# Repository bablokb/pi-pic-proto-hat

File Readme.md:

The Pi-PIC-Proto-Hat (Version 2)
================================

Overview
--------

One of the shortcomings of the Pi is it's inability to turn off power after
shutdown. While the Pi itself only drains a small amount of power, attached
peripherals might draw a lot more. At irregular intervals, the Pi also
fails to shutdown the USB-connector, so USB-devices can really use large
amounts of power even when the Pi has shutdown.

One solution is to pull the plug, another one uses a mosfet controlled by
a microcontroller to turn power on and off. The MCU typically uses its
GPIOs to receive external signals for power on and off. In its simplest
form such a signal is just a button pulling the GPIO to ground.

The pi-pic-proto-hat provides the wiring for a PIC12F675 (MCU) and the
IRF4905 (mosfet). In addition, there is a small prototyping area for
buttons, sensors and alike.

If you are more familiar with a different family of MCUs (e.g. Atmega), you
should modify the design of the pcb. The Kicad-sources are in the
directory `pi-pic-proto-hat.kicad`.

Design
------

The design consists mainly of the two parts "power supply" and "PIC".
The PIC part

is a fairly standard implementation for the PIC featuring an
ICSP (in-circuit-programming) connector J8. GP2 and GP4 are connected to
connector, GP4 in addition to a switch and the interupt-pin of the RTC.
GP3 is only connected to the ICSP connector and unused otherwise.

If you are not using a MCU of the PIC-family, this is the part you must
modify to fit your preferred MCU.

The power-supply part

connects a barrel-jack J6 (5mm/2.1mm-type) to the mosfet, which controls
the 5V and 3.3V connectors of the Pi. J6 is also connected to J3/J11, which
give you 5V independent of the state of the Pi. In addition, if you
populate the 1117-regulator (U2), you also have permanent 3.3V on
connectors J4/J5.

The IRF4905 mosfet will switch power efficiently as long as the voltage
of the gate is high enough. The 5V of the MCU is sufficient and the
mosfet will not get too warm with the typical currents needed by a Pi.

The pcb also provides access to most of the GPIOs of the Pi. In addition,
there is a prototyping area and a number of GND-pins and power pins
(5V and 3,3V).

Note that the project-directory contains a Fritzing-template
(prototype-template.fzz) which is useful for prototyping:

Manufacturing
-------------

If your pcb-manufacturer supports Kicad directly, you can just upload the
project-file. Otherwise you have to start Kicad and export ("plot") the
gerber-files for the pcb (gerber is a universal format understood by all
manufacturers).

When you use the existing pcb-layout without any modifications, you should
make sure that you have the correct parts available. Most critical is the
barrel-jack footprint. The pcb is designed for the CUI_PJ_102AH. This part
is available e.g. from Adafruit. It looks like a normal barrel-jack adapter
but has smaller pins so you can use it directly on a breadboard.

Part-List
---------

|Part                | Value           | Number | Remark               |
|--------------------|-----------------|--------|----------------------|
|C1,C4               | 100nF/50V       | 2      | SMD 1206             |
|C2,C3               | 10µF            | 2      | SMD 1206 Tantal      |
|D1,D2               | LED             | 2      | SMD 1206             |
|J1-J5,J7-13         | SL 1x40G 2,54mm | 2      | vertical             |
|J6 (barral jack)    | CUI_PJ_102AH    | 1      | Adafruit             |
|P1 (Pi-socket)      | BL 2x20G 2,54mm | 1      | vertical             |
|Q1                  | IRF4905         | 1      | TO-220AB             |
|R1,R6               | 10k             | 2      | SMD 1206             |
|R2,R3,R4,R5         | 1k              | 4      | SMD 1206             |
|R7                  | 6.2k            | 1      | SMD 1206             |
|R8                  | 12k             | 1      | SMD 1206             |
|SW1                 |                 | 1      | slim switch          |
|U1                  | PIC12F675-IP    | 1      | SO-8                 |
|U2                  | TLV1117-33      | 1      | SOT-223 (or AMS1117) |
|U3                  | DS3231M         | 1      | SOIC-16W             |

Wiring
------

Not all parts are necessary, e.g. you don't need to populate the RTC
or the regulator. The two LEDs D2 (active power-supply) and D1 (power
is provided to the Pi) are also optional (together with their resistors).

You need to close jumper J1 (Run/~PGM) during normal operation. If you
flash the firmware, this jumper should be open.

Please be careful not to power the hat and the Pi at the same time.

Flashing a Firmware
-------------------

The required firmware for the PIC depends on the specific setup you choose.
In the directory [pic-firmware](./pic-firmware/Readme.md)
you will find a ready to flash hex-file for the PIC.

For flashing, you need a PICkit2-programmer, available for a few bucks from
ebay. You can flash from Linux/Raspbian with the program `pk2cmd`. The hat
has a connector for the ICSP-programmer. You should remove the jumper-shim
on J1 (connection to Pi) during programming.

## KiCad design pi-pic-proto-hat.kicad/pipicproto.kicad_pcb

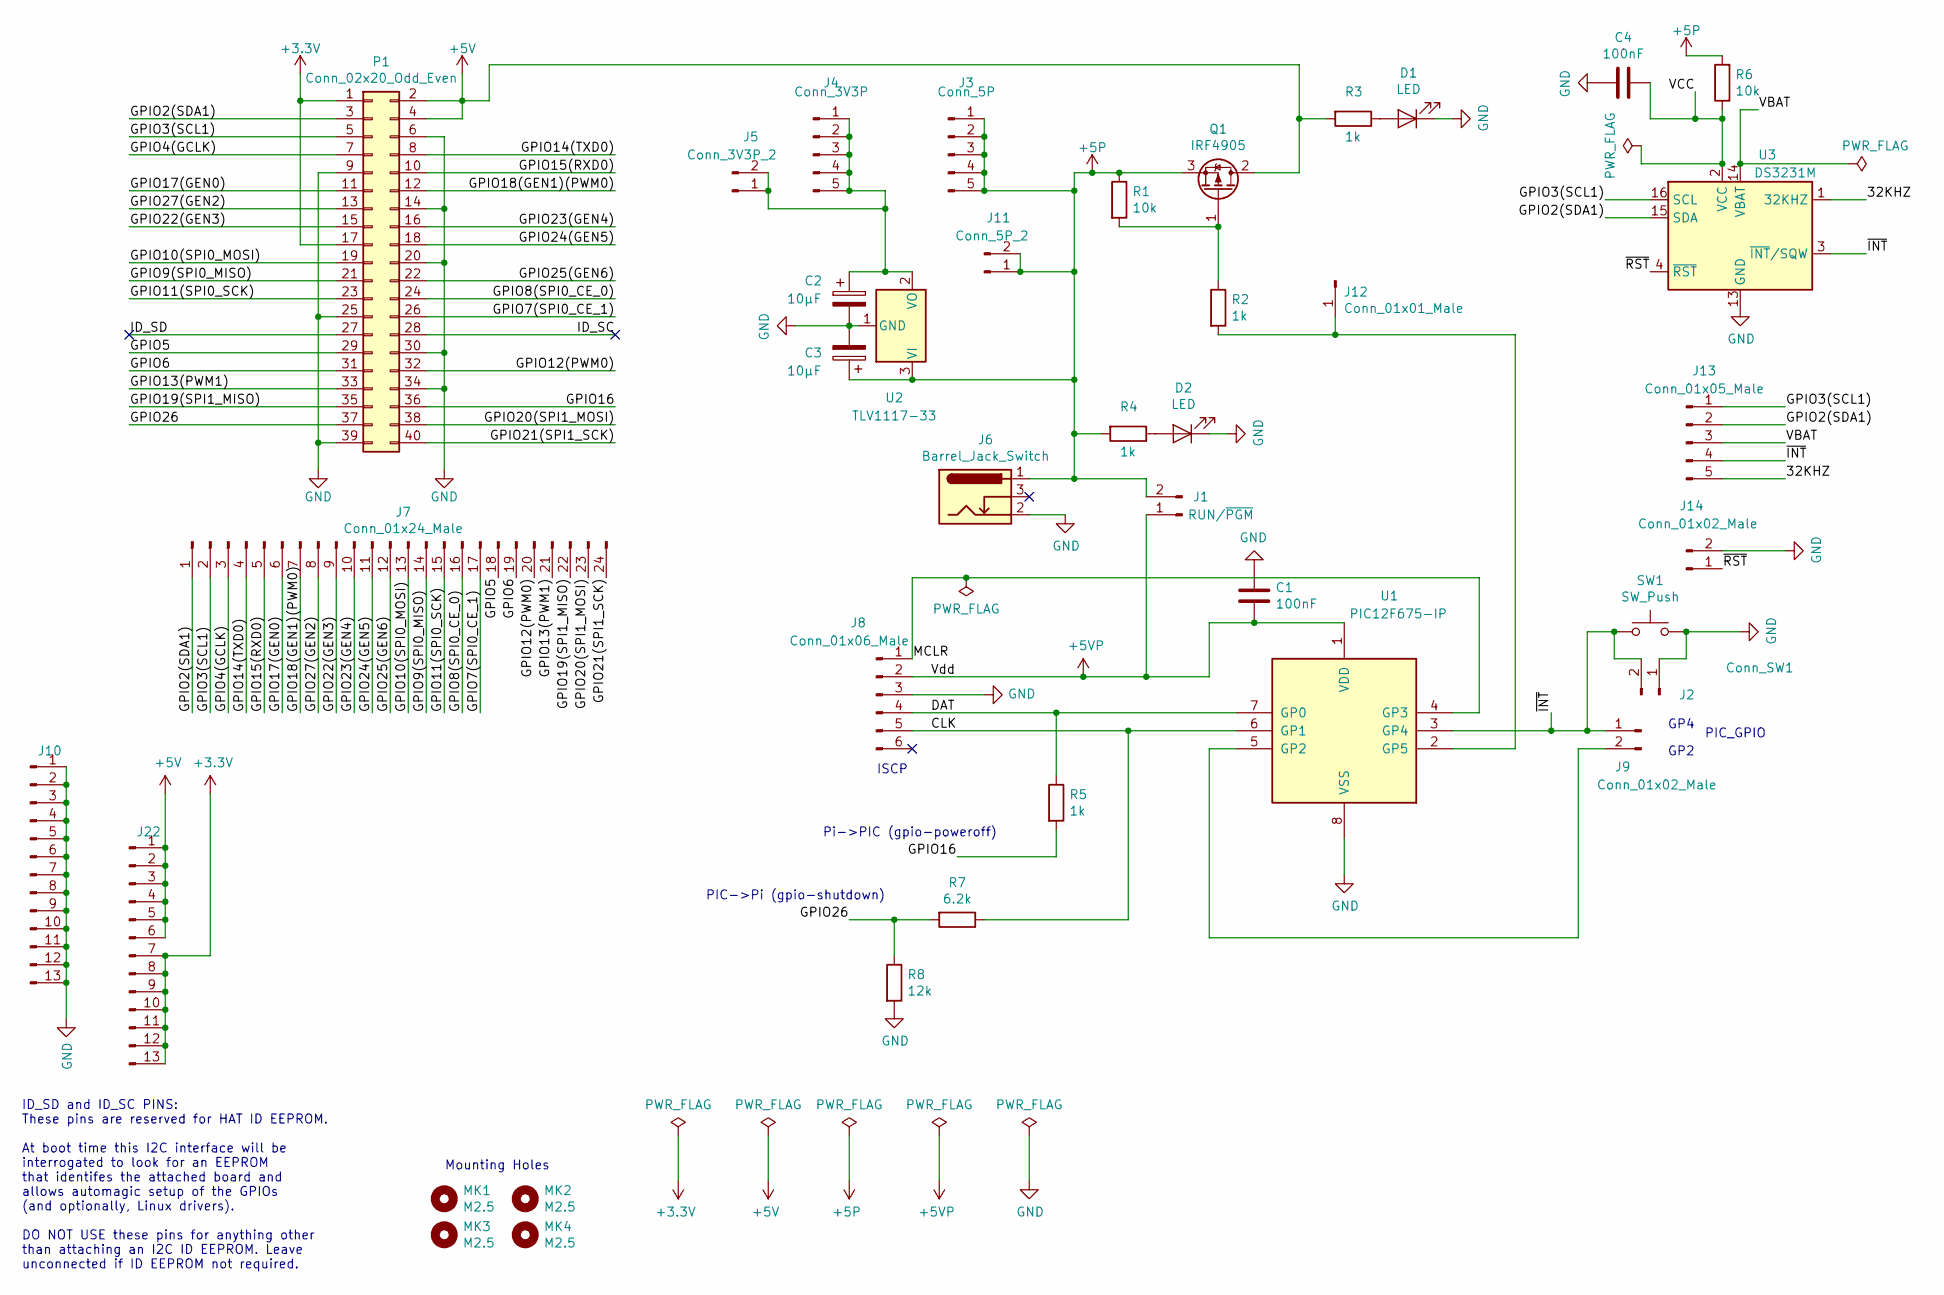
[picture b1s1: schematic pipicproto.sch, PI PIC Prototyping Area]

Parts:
C1, C4: 100nF; C_1206_3216Metric_Pad1.42x1.75mm_HandSolder
C2, C3: 10µF; CP_EIA-3216-18_Kemet-A
D1, D2: LED; LED_1206_3216Metric_Pad1.42x1.75mm_HandSolder
J1: RUN/~PGM~; PinHeader_1x02_P2.54mm_Vertical
J2: Conn_SW1; PinHeader_1x02_P2.54mm_Vertical
J3: Conn_5P; PinHeader_1x05_P2.54mm_Vertical
J4: Conn_3V3P; PinHeader_1x05_P2.54mm_Vertical
J5: Conn_3V3P_2; PinHeader_1x02_P2.54mm_Vertical
J6: Barrel_Jack_Switch; BarrelJack_CUI_PJ-102AH_Horizontal
J7: Conn_01x24_Male; PinHeader_1x24_P2.54mm_Vertical
J8: Conn_01x06_Male; PinHeader_1x06_P2.54mm_Vertical
J9, J14: Conn_01x02_Male; PinHeader_1x02_P2.54mm_Vertical
J10, J22: Conn_01x13_Male; PinHeader_1x13_P2.54mm_Vertical
J11: Conn_5P_2; PinHeader_1x02_P2.54mm_Vertical
J12: Conn_01x01_Male; PinHeader_1x01_P2.54mm_Vertical
J13: Conn_01x05_Male; PinHeader_1x05_P2.54mm_Vertical
MK1, MK2, MK3, MK4: M2.5; MountingHole_2.7mm_M2.5
P1: Conn_02x20_Odd_Even; PinSocket_2x20_P2.54mm_Vertical
Q1: IRF4905; TO-220-3_Vertical
R1, R6: 10k; R_1206_3216Metric_Pad1.42x1.75mm_HandSolder
R2, R3, R4, R5: 1k; R_1206_3216Metric_Pad1.42x1.75mm_HandSolder
R7: 6.2k; R_1206_3216Metric_Pad1.42x1.75mm_HandSolder
R8: 12k; R_1206_3216Metric_Pad1.42x1.75mm_HandSolder
SW1: SW_Push; SW_PUSH_SLIM_1x4
U1: PIC12F675-IP; SO-8_3.9x4.9mm_P1.27mm
U2: TLV1117-33; SOT-223
U3: DS3231M; SOIC-16W_7.5x10.3mm_P1.27mm

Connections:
+3V3: J22.7, J22.8, J22.9, J22.10, J22.11, J22.12, J22.13, P1.1, P1.17
+5P: C3.1, J1.2, J3.1, J3.2, J3.3, J3.4, J3.5, J6.1, J11.1, J11.2, Q1.3 (S), R1.1, R4.2, R6.2, U2.3 (VI)
+5V: J22.1, J22.2, J22.3, J22.4, J22.5, J22.6, P1.2, P1.4, Q1.2 (D), R3.2
+5VP: C1.2, J1.1, J8.2, U1.1 (VDD)
/32KHZ: J13.5, U3.1 (32KHZ)
/CLK: J8.5, R7.1, U1.6 (GP1)
/DAT: J8.4, R5.1, U1.7 (GP0)
/GPIO2(SDA1): J7.1, J13.2, P1.3, U3.15 (SDA)
/GPIO3(SCL1): J7.2, J13.1, P1.5, U3.16 (SCL)
/GPIO4(GCLK): J7.3, P1.7
/GPIO5: J7.18, P1.29
/GPIO6: J7.19, P1.31
/GPIO7(SPI0_CE_1): J7.17, P1.26
/GPIO8(SPI0_CE_0): J7.16, P1.24
/GPIO9(SPI0_MISO): J7.14, P1.21
/GPIO10(SPI0_MOSI): J7.13, P1.19
/GPIO11(SPI0_SCK): J7.15, P1.23
/GPIO12(PWM0): J7.20, P1.32
/GPIO13(PWM1): J7.21, P1.33
/GPIO14(TXD0): J7.4, P1.8
/GPIO15(RXD0): J7.5, P1.10
/GPIO16: P1.36, R5.2
/GPIO17(GEN0): J7.6, P1.11
/GPIO18(GEN1)(PWM0): J7.7, P1.12
/GPIO19(SPI1_MISO): J7.22, P1.35
/GPIO20(SPI1_MOSI): J7.23, P1.38
/GPIO21(SPI1_SCK): J7.24, P1.40
/GPIO22(GEN3): J7.9, P1.15
/GPIO23(GEN4): J7.10, P1.16
/GPIO24(GEN5): J7.11, P1.18
/GPIO25(GEN6): J7.12, P1.22
/GPIO26: P1.37, R7.2, R8.1
/GPIO27(GEN2): J7.8, P1.13
/ID_SC: P1.28
/ID_SD: P1.27
/MCLR: J8.1, U1.4 (GP3)
/VBAT: J13.3, U3.14 (VBAT)
/VCC: C4.1, R6.1, U3.2 (VCC)
/~INT: J2.2, J9.1, J13.4, SW1.1, U1.3 (GP4), U3.3 (~INT~/SQW)
/~RST: J14.1, U3.4 (~RST)
GND: C1.1, C2.2, C3.2, C4.2, D1.1 (K), D2.1 (K), J2.1, J6.2, J8.3, J10.1, J10.2, J10.3, J10.4, J10.5, J10.6, J10.7, J10.8, J10.9, J10.10, J10.11, J10.12, J10.13, J14.2, P1.6, P1.9, P1.14, P1.20, P1.25, P1.30, P1.34, P1.39, R8.2, SW1.2, U1.8 (VSS), U2.1 (GND), U3.5 (GND), U3.6 (GND), U3.7 (GND), U3.8 (GND), U3.9 (GND), U3.10 (GND), U3.11 (GND), U3.12 (GND), U3.13 (GND)
unnamed: C2.1, J4.1, J4.2, J4.3, J4.4, J4.5, J5.1, J5.2, U2.2 (VO)
unnamed: D1.2 (A), R3.1
unnamed: D2.2 (A), R4.1
unnamed: J9.2, U1.5 (GP2)
unnamed: J12.1, R2.2, U1.2 (GP5)
unnamed: Q1.1 (G), R1.2, R2.1

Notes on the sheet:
ID_SD and ID_SC PINS: These pins are reserved for HAT ID EEPROM. At boot time this I2C interface will be interrogated to look for an EEPROM that identifes the attached board and allows automagic setup of the GPIOs (and optionally, Linux drivers). DO NOT USE these pins for anything other than attach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
Mounting Holes
PIC_GPIO
ISCP
Pi->PIC (gpio-poweroff)
PIC->Pi (gpio-shutdown)
GP4
GP2

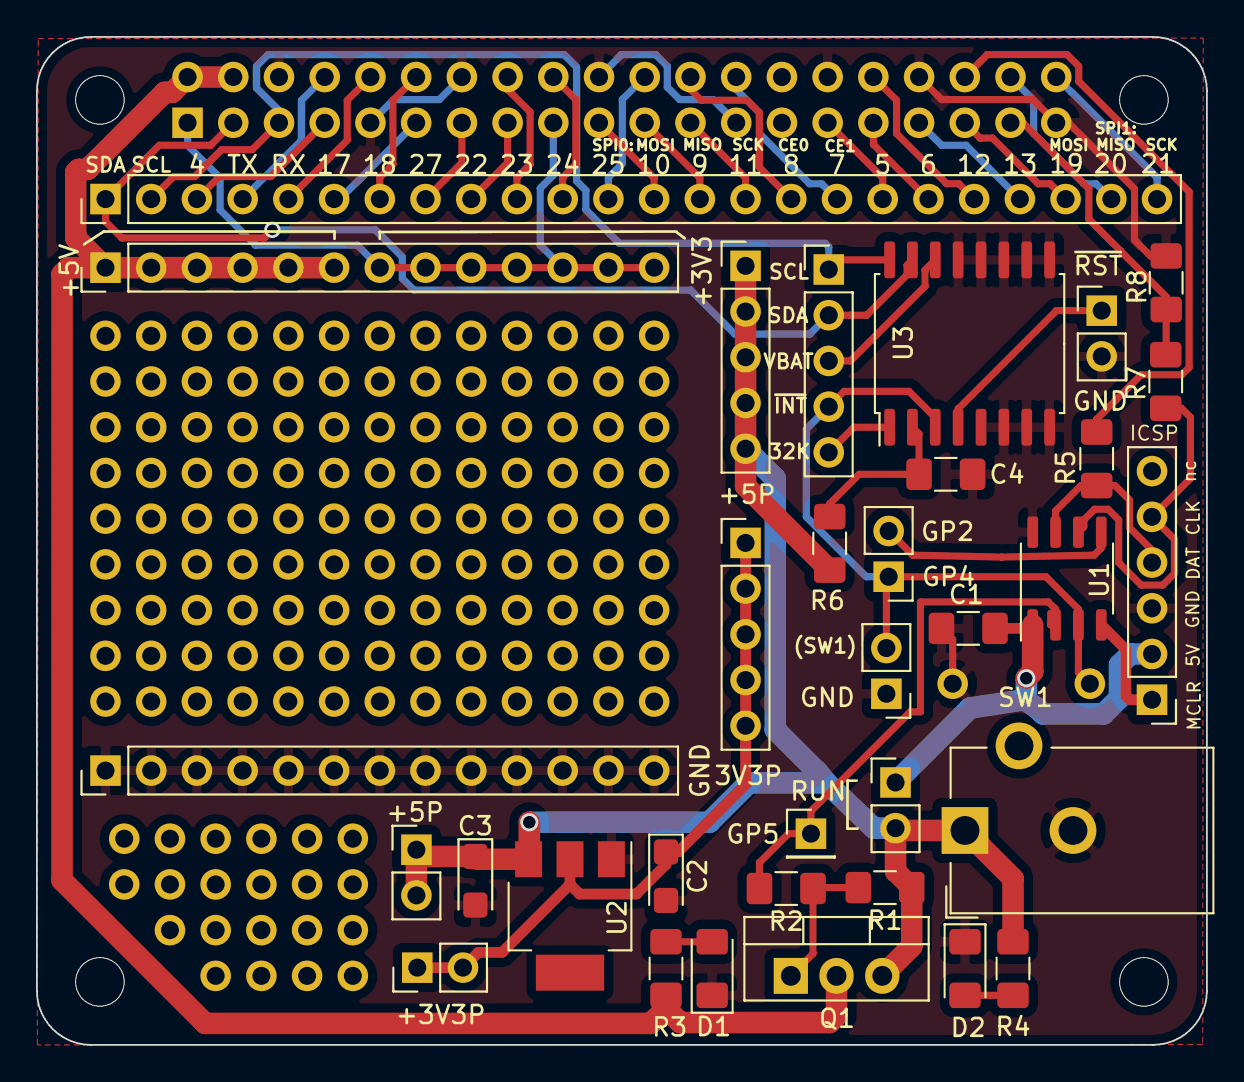
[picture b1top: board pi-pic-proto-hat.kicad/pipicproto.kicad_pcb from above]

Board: 2 copper layers, 65.0 x 56.0 mm, 39 parts (1 on the bottom side), 45 nets.

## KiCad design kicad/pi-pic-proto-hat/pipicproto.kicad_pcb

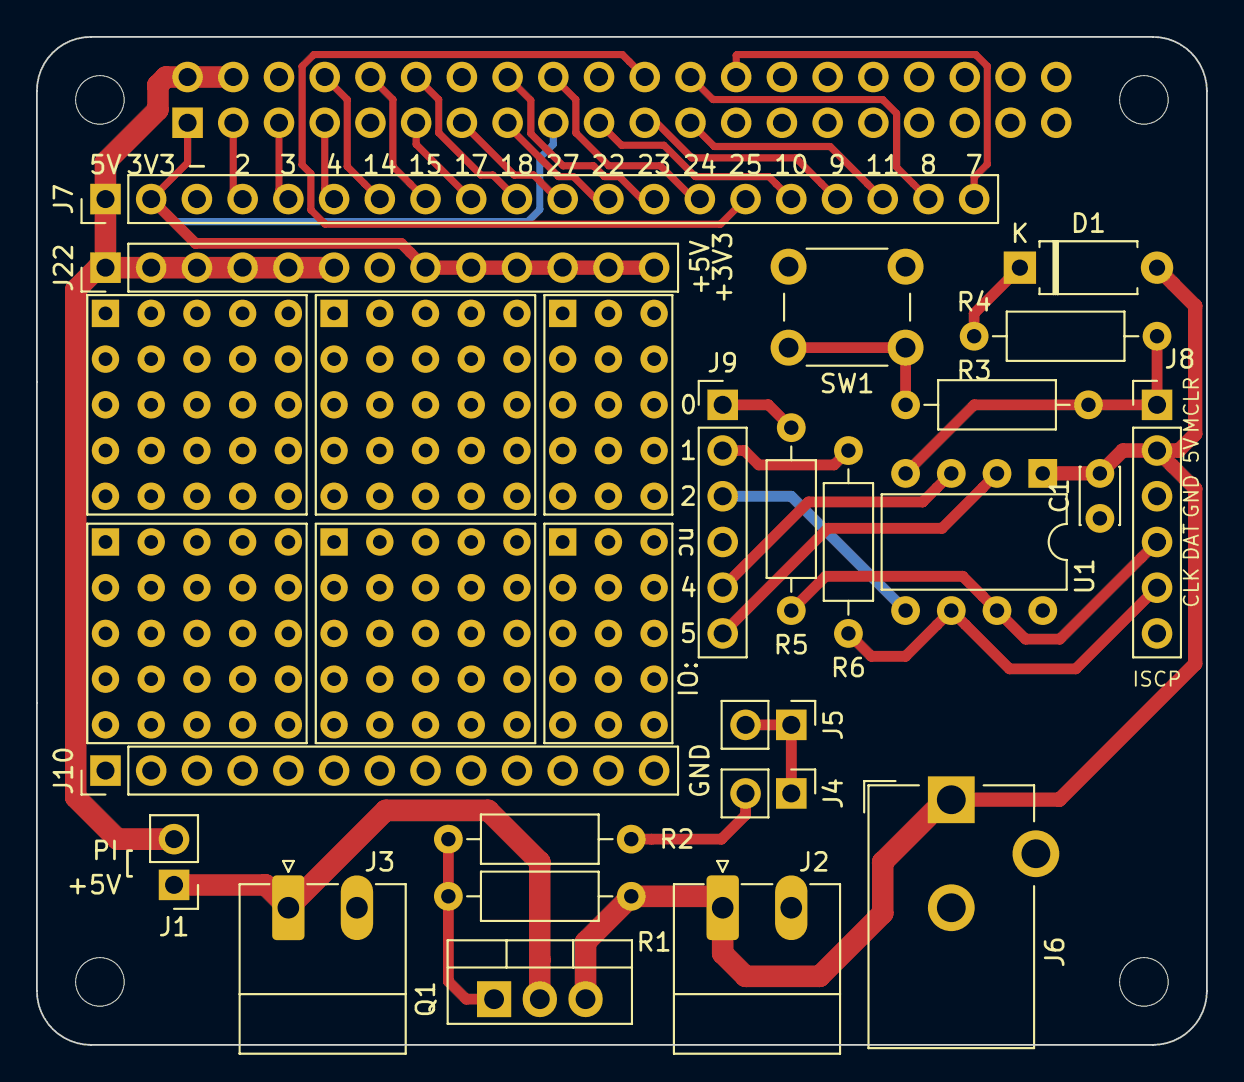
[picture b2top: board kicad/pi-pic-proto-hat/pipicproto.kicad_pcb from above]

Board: 2 copper layers, 65.0 x 56.0 mm, 27 parts (1 on the bottom side), 35 nets.

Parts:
C1: 100n; C_Disc_D3.0mm_W2.0mm_P2.50mm
D1: D_Schottky; D_A-405_P7.62mm_Horizontal
J1, J4, J5: Conn_01x02_Male; PinHeader_1x02_P2.54mm_Vertical
J2, J3: Conn_01x02_Male; PhoenixContact_MC_1,5_2-G-3.81_1x02_P3.81mm_Horizontal
J6: Barrel_Jack_Switch; BarrelJack_CUI_PJ-102AH_Horizontal
J7: Conn_01x20_Male; PinHeader_1x20_P2.54mm_Vertical
J8, J9: Conn_01x06_Male; PinHeader_1x06_P2.54mm_Vertical
J10, J22: Conn_01x13_Male; PinHeader_1x13_P2.54mm_Vertical
MK1, MK2, MK3, MK4: M2.5; MountingHole_2.7mm_M2.5
P1: Conn_02x20_Odd_Even; PinSocket_2x20_P2.54mm_Vertical
Q1: IRF4905; TO-220-3_Vertical
R1: 10k; R_Axial_DIN0207_L6.3mm_D2.5mm_P10.16mm_Horizontal
R2, R3, R5, R6: 1k; R_Axial_DIN0207_L6.3mm_D2.5mm_P10.16mm_Horizontal
R4: 22k; R_Axial_DIN0207_L6.3mm_D2.5mm_P10.16mm_Horizontal
SW1: SW_Push; SW_PUSH_6mm_H9.5mm
U1: PIC12F675-IP; DIP-8_W7.62mm

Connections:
+3V3: J7.2, J22.8, J22.9, J22.10, J22.11, J22.12, J22.13, P1.1, P1.17
+5V: J1.2, J7.1, J22.1, J22.2, J22.3, J22.4, J22.5, J22.6, P1.2, P1.4
+5VP: C1.2, D1.2, J2.1, J6.1, J8.2, Q1.3, R1.1, U1.1
/CLK: J8.5, R6.1, U1.6
/DAT: J8.4, R5.1, U1.7
/GPIO2(SDA1): J7.4, P1.3
/GPIO3(SCL1): J7.5, P1.5
/GPIO4(GCLK): J7.6, P1.7
/GPIO7(SPI1_CE_N): J7.20, P1.26
/GPIO8(SPI0_CE_N): J7.19, P1.24
/GPIO9(SPI0_MISO): J7.17, P1.21
/GPIO10(SPI0_MOSI): J7.16, P1.19
/GPIO11(SPI0_SCK): J7.18, P1.23
/GPIO14(TXD0): J7.7, P1.8
/GPIO15(RXD0): J7.8, P1.10
/GPIO17(GEN0): J7.9, P1.11
/GPIO18(GEN1)(PWM0): J7.10, P1.12
/GPIO22(GEN3): J7.12, P1.15
/GPIO23(GEN4): J7.13, P1.16
/GPIO24(GEN5): J7.14, P1.18
/GPIO25(GEN6): J7.15, P1.22
/GPIO27(GEN2): J7.11, P1.13
/IO0: J9.1, R5.2
/IO1: J9.2, R6.2
/IO2: J9.3, U1.5
/IO4: J9.5, U1.3
/IO5: J9.6, U1.2
/MCLR: J8.1, R3.1, R4.1, U1.4
GND: C1.1, J2.2, J3.2, J6.2, J7.3, J8.3, J10.1, J10.2, J10.3, J10.4, J10.5, J10.6, J10.7, J10.8, J10.9, J10.10, J10.11, J10.12, J10.13, P1.6, P1.9, P1.14, P1.20, P1.25, P1.30, P1.34, P1.39, SW1.2, U1.8
unnamed: D1.1, R4.2
unnamed: J1.1, J3.1, Q1.2
unnamed: J4.1, J5.1, J5.2
unnamed: J4.2, R2.2
unnamed: Q1.1, R1.2, R2.1
unnamed: R3.2, SW1.1

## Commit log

2020-02-17 version-a: initial commit
2020-02-17 version-b
2020-02-17 version-d
2020-02-17 version-e
2020-02-17 version-f (F.Cu filled, B.SilkS labels)
2020-02-22 renamed (and moved) directory kicad/pi-pic-proto-hat to pi-pic-proto-hat.kicad
2020-03-09 updated version with wait after power-on
2020-03-10 added content
2020-03-10 added descriptive text
2020-03-11 moved directory
2020-03-11 moved files
2020-03-11 moved labels
2020-03-11 added link to Fritzing-view
2020-03-11 fixed link after moving target directory
2020-03-11 added description of prototype template
2020-03-12 document Pi-configuration (additional lines in config.txt)
2020-03-12 small fixes
2020-03-12 bugfix: power is on if gate is low
2020-03-12 also link to pcb.jpg
2020-03-12 fixed spelling
2020-04-13 added section 'Part list'
2020-06-19 added V1 to title
2020-06-19 added 'Development branch' to title
2020-06-22 fix: changed label ISCP to ICSP
2020-06-22 V2.01: removed J4/J5/prototyping area
2020-06-22 V2.02: connect GP0/GP1 directly to the Pi (add voltage-divider for GP1)
2020-06-22 V2.03: removed reset-button, pullup, bat85
2020-06-22 moved voltage-divider to free area above PIC
2020-06-22 V2.04: place jumper J1 between J6 (barrel-jack) and ICSP-connector
2020-06-29 V2.06: remove R6 (not needed, since we added a voltage-divider)
2020-07-03 V2.07: remove J2/J3 connectors
2020-07-03 V2.08: migrate to SMD for PIC
2020-07-03 V2.09: rotated ICSP-header to optimze layout
2020-07-03 V2.10: changed place of GP2/GP4 header
2020-07-17 moved R7/R8 to top right
2020-07-17 moved R5/PIC next to ICSP
2020-07-18 V2.11: added LEDs
2020-07-18 V2.12: changed position of RUN-jumper
2020-07-23 V2.13: added button connected to GP2
2020-07-23 moved button to right of power-jack
2020-07-24 V2.14: removed dead button from power connector
2020-07-24 V2.15: added connector for +5P (5V permanently on)
2020-07-24 V2.16: added regulator and connector for +3V3P (3V3 permanently on)
2020-07-25 V2.17: connect switch to GP4 instead of GP2
2020-07-25 added prototyping area
2020-07-25 V2.18: add 5VP and 3V3P connectors bottom left
2020-07-25 added prototyping area bottom left
2020-07-25 V2.19: add GP5 connector
2020-07-30 V2.20: added DS3231
2020-08-01 V2.21: added 32KHZ-pin of RTC to connector
2020-08-01 V2.22: added RST/GND connector for RTC
2020-08-12 moved some labels
2020-08-18 fixed label on bottom
2020-08-22 updated for new version
2020-08-22 non-functional changes to layout
2020-08-22 added note about status of Readme
2020-08-30 not relevant for v2
2020-08-30 add section 'Pi Configuration'
2020-08-30 removed temporarily
2020-08-30 changed header-levels
2020-08-30 updated to v2
2020-08-30 link to schematic
2020-08-30 updated for v2
2021-03-30 fixed link to source
